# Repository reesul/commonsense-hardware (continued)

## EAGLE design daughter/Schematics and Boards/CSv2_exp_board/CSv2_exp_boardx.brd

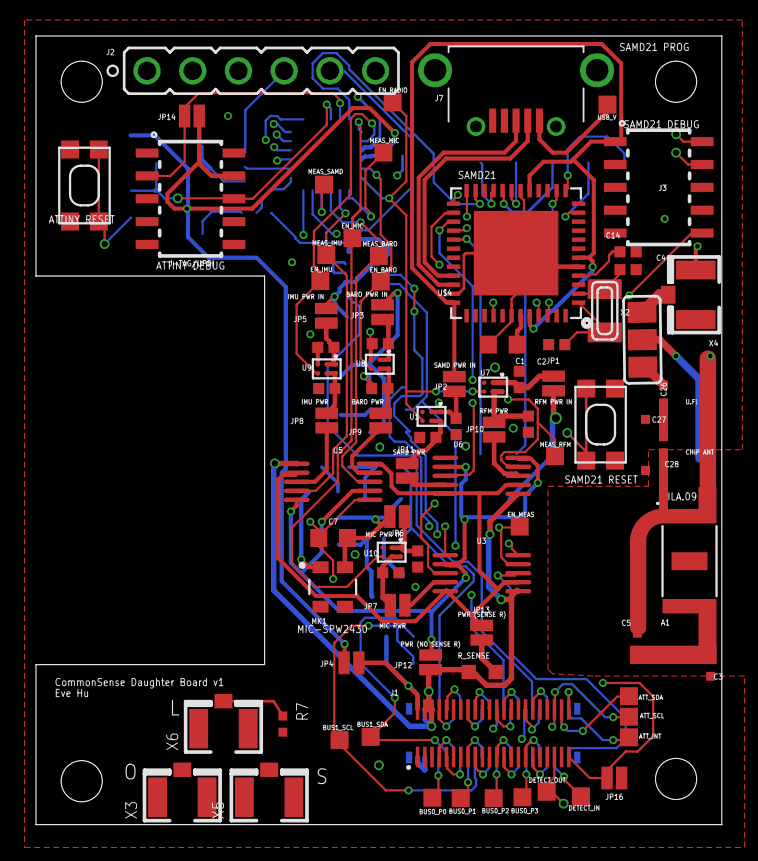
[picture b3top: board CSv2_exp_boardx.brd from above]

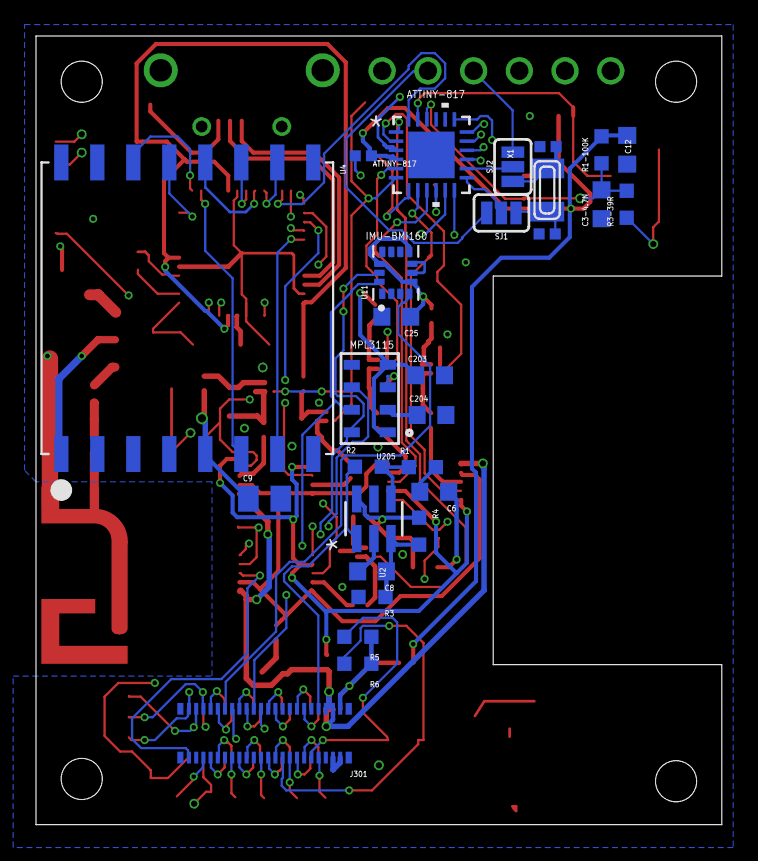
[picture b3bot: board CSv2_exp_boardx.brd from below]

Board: 4 copper layers, 38.1 x 43.8 mm, 112 parts (28 on the bottom side), 108 nets.

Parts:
A1: ILA09_CHIP_ANTENNA; ILA_09_CHIP_ANTENNA2
ATTINY-817: ATTINY817-MFRQFN24_RX4MC-L_ATTINY817-MFR; ATTINY817-MFRQFN24_RX4MC-L_QFN24_4X4MC
ATT_INT: TPTP10SQ; TP10SQ
ATT_SCL: TPTP10SQ; TP10SQ
ATT_SDA: TPTP10SQ; TP10SQ
BUS0_P0, BUS0_P1, BUS0_P2, BUS0_P3, BUS1_SCL, BUS1_SDA: TPTP10SQ; TP10SQ
C1: 1uF; C0603
C2, C4: 22pF; C0402
C3: 3.9p; C0402-S
C3-4.7N: 4.7n; C0603
C5: 2.2p; C0402-S
C6: 4.7u; C0603
C7: 0.1u; C0603
C8: 1u; C0603
C9: 10uF; C0805
C10, C17, C19, C21, C23: 1u; C0402
C11, C18, C20, C22, C24: 100n; C0402
C12: 4.7nF; C0603
C13: 100nF; C0402
C14: 1uF; C0402
C15, C16: 13pF; C0402
C25, C203, C204: 0.1uF; C0603
C26, C27, C28: C0402-S
DETECT_IN: TPTP10SQ; TP10SQ
DETECT_OUT: TPTP10SQ; TP10SQ
EN_BARO: TPTP10SQ; TP10SQ
EN_IMU: TPTP10SQ; TP10SQ
EN_MEAS: TPTP10SQ; TP10SQ
EN_MIC: TPTP10SQ; TP10SQ
EN_RADIO: TPTP10SQ; TP10SQ
J1: HIROSE-DF40_44-PIN_CONNECTORS-RECEPTACLE; HRS_DF40HC(3.0)-44DS-0.4V(51)
J2: J-SERIAL-PORT; HEADER-1X6
J3: CORTEX_DEBUG_SMD; SAMTECH_FTSH-105-01
J7: J-USB-HIROSE-MICRO-USB; USB-THRU-ZX62D-AB-5P8
J301: HIROSE-DF40_44-PIN_CONNECTORS-HEADER; HRS_DF40C-44DP-0.4V(51)
J-TAG/UPDI: ATTINY_AVR_DEBUG_SMD; ATTINY_AVR_DEBUG
JP1, JP2, JP3, JP4, JP5, JP6, JP7, JP8, JP9, JP10, JP11, JP12, JP13: JUMPER-SMT_2_NC_PASTELG_NO-SILK; SMT-JUMPER_2_NC_PASTE_NO-SILK
JP14, JP16: JUMPER-SMT_2_NO_PASTEFREE; SMT-JUMPER_2_NO_PASTEFREE_NO-SILK
L1: L0402
MEAS_BARO: TPTP10SQ; TP10SQ
MEAS_IMU: TPTP10SQ; TP10SQ
MEAS_MIC: TPTP10SQ; TP10SQ
MEAS_RFM: TPTP10SQ; TP10SQ
MEAS_SAMD: TPTP10SQ; TP10SQ
MK1: SPW2430HR5H-B; MIC_SPW2430HR5H-B
R1: 1.5k; R0603
R1-100K, R2: 100k; R0603
R3, R4: 10k; R0603
R3-39R: 39r; R0603
R5, R6: 4.7k; R0603
R7: R0402
R_SENSE: 1.33; R0603
SJ1, SJ2: JUMPER-SMT_3_1-NC_PASTE_SILK; SMT-JUMPER_3_1-NC_PASTE_SILK
SJ3: JUMPER_SJ_2
SW1, SW2: SPST_TACT-KMR2; KMR2
U1, U7, U8, U9, U10: LOADSWITCH-MIC94164; WLCSP6_2X3
U2: ADA4841-1YRJZ-R7; RJ_6
U3, U5, U6: Value; DGS0010A_L
U4: RFM69HCW; RFM-MOD
U11: BMI160; PQFN50P300X250X88-14N
U205: MPL3115A2; MPL3115A2_PSON125P300X500X120-8N
U$4: ATSAMD21G18_QFN; MICROBUILDER_TQFN48_7MM
USB_V: TPTP10SQ; TP10SQ
X1: 32.768kHz; ADAFRUIT2_XTAL3215
X2: 32.768; ADAFRUIT2_XTAL3215
X3, X4, X5, X6: uFL; U.FL

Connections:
+3V3_ATT: ATTINY-817.4, C12.2, C13.2, J-TAG/UPDI.4, JP4.2, JP14.1, R1-100K.2
+3V3_BARO: C203.1, JP3.2, U205.1, U205.4
+3V3_BARO_IN: C19.1, JP9.2, U8.A2, U8.B2
+3V3_BARO_OUT: C20.1, JP3.1, U8.A1, U8.B1
+3V3_BARO_PWR: JP9.1, U5.9
+3V3_DTR: J1.4, J1.6, J301.4, J301.6, JP12.1, R_SENSE.1, U3.1, U5.1, U6.1
+3V3_DTR0: J1.2, J301.2, JP4.1, R5.1, R6.1
+3V3_IMU: C25.1, JP5.2, U11.5, U11.8, U11.12
+3V3_IMU_IN: C21.1, JP8.2, U9.A2, U9.B2
+3V3_IMU_OUT: C22.1, JP5.1, U9.A1, U9.B1
+3V3_IMU_PWR: JP8.1, U5.3
+3V3_MEAS: JP13.2, U3.2, U3.10, U5.2, U5.10, U6.2, U6.10
+3V3_MIC: C7.1, JP6.2, MK1.4, R4.1, U2.6
+3V3_MIC_IN: C23.1, JP7.2, U10.A2, U10.B2
+3V3_MIC_OUT: C24.1, JP6.1, U10.A1, U10.B1
+3V3_MIC_PWR: JP7.1, U3.9
+3V3_NMEAS: JP12.2, U3.7, U5.5, U5.7, U6.5, U6.7
+3V3_RFM: C9.1, JP1.2, U4.5P
+3V3_RFM_IN: C17.1, JP10.2, U7.A2, U7.B2
+3V3_RFM_OUT: C18.1, JP1.1, U7.A1, U7.B1
+3V3_RFM_PWR: JP10.1, U6.3
+3V3_SAMD: J3.1, JP2.2, U$4.6, U$4.17, U$4.36, U$4.44
+3V3_SAMD_IN: C10.1, JP11.2, U1.A2, U1.B2
+3V3_SAMD_OUT: C11.1, JP2.1, U1.A1, U1.B1
+3V3_SAMD_PWR: JP11.1, U6.9
AREF: C14.1, U$4.4
ATT_INT: ATTINY-817.17, ATT_INT.TP, J1.44, J301.44
AT_RESET: ATTINY-817.22, C3-4.7N.2, J-TAG/UPDI.6, R1-100K.1, R3-39R.2
AT_UPDI: ATTINY-817.23, J-TAG/UPDI.3, JP14.2
BUS0_AIN0: J301.8, R2.1, U2.1
BUS0_GPIO0: ATTINY-817.24, J301.24, U$4.23
BUS0_GPIO1: J301.32, U$4.24
BUS0_SERCOM_P0: BUS0_P0.TP, J301.7, U$4.25
BUS0_SERCOM_P1: BUS0_P1.TP, J301.15, U$4.26
BUS0_SERCOM_P2: BUS0_P2.TP, J301.23, U$4.27
BUS0_SERCOM_P3: BUS0_P3.TP, J301.31, U$4.28
BUS1_GPIO0: J301.26, U205.6
BUS1_GPIO1: J301.34, U11.4
BUS1_SERCOM_P0: BUS1_SDA.TP, J301.9, R5.2, U11.14, U205.7
BUS1_SERCOM_P1: BUS1_SCL.TP, J301.17, R6.2, U11.13, U205.8
BUS2_AIN0: J1.8, J301.12
BUS2_AIN1: J1.16, J301.20
BUS2_GPIO0: J1.24, J301.28
BUS2_GPIO1: J1.32, J301.36
BUS2_SERCOM_P0: J1.7, J301.11
BUS2_SERCOM_P1: J1.15, J301.19
BUS2_SERCOM_P2: J1.23, J301.27
BUS2_SERCOM_P3: J1.31, J301.35
BUS3_AIN0: J1.10, J301.14
BUS3_AIN1: J1.18, J301.22
BUS3_GPIO0: J1.26, J301.30
BUS3_GPIO1: J1.34, J301.38
BUS3_SERCOM_P0: J1.9, J301.13
BUS3_SERCOM_P1: J1.17, J301.21
BUS3_SERCOM_P2: J1.25, J301.29
BUS3_SERCOM_P3: J1.33, J301.37
DTR_DETECT_IN: ATTINY-817.18, DETECT_IN.TP, J301.39
DTR_DETECT_OUT: ATTINY-817.19, DETECT_OUT.TP, J1.39
D_N: J7.D-, U$4.33
D_P: J7.D+, U$4.34
EN_BARO: ATTINY-817.5, EN_BARO.TP, U8.C2
EN_IMU: ATTINY-817.2, EN_IMU.TP, U9.C2
EN_MEAS: ATTINY-817.12, EN_MEAS.TP, U3.4
EN_MIC: ATTINY-817.1, EN_MIC.TP, U10.C2
EN_RADIO: ATTINY-817.6, EN_RADIO.TP, U1.C2, U7.C2
GND: A1.G1, ATTINY-817.3, C1.2, C2.2, C3.1, C3-4.7N.1, C4.2, C5.1, C7.2, C8.2, C9.2, C10.2, C11.2, C12.1, C13.1, C14.2, C15.1, C16.1, C17.2, C18.2, C19.2, C20.2, C21.2, C22.2, C23.2, C24.2, C25.2, C27.2, C28.1, C28.2, C203.2, C204.2, J1.1, J1.3, J1.5, J2.1, J3.3, J3.5, J7.GND, J7.S1, J7.S2, J7.S3, J7.S4, J301.1, J301.3, J301.5, J-TAG/UPDI.2, JP16.1, L1.2, MK1.2, MK1.3, R3.2, R7.2, SW1.1, SW1.3, SW2.1, SW2.3, U1.C1, U2.2, U3.6, U4.2P, U4.9P, U4.16P, U5.6, U6.6, U7.C1, U8.C1, U9.C1, U10.C1, U11.1, U11.6, U11.7, U205.3, U$4.5, U$4.18, U$4.35, U$4.42, U$4.THERMAL, X3.1, X3.2, X4.1, X4.2, X5.1, X5.2, X5.3, X6.1, X6.2
IN+: C8.1, R3.1, R4.2, U2.3
IN-: R1.1, R2.2, U2.4
LORA_CS: U4.13P, U$4.11
LORA_IRQ0: U4.6P, U$4.14
LORA_IRQ1: U4.7P, U$4.29
LORA_MISO: U4.10P, U$4.21
LORA_MOSI: U4.11P, U$4.19
LORA_RST: U4.14P, U$4.13
LORA_SCK: U4.12P, U$4.20
MASTER_I2C_SCL: ATTINY-817.16, ATT_SCL.TP, J1.40, J301.40
MASTER_I2C_SDA: ATTINY-817.15, ATT_SDA.TP, J1.42, J301.42
MEAS_BARO: ATTINY-817.9, MEAS_BARO.TP, U5.8
MEAS_IMU: ATTINY-817.8, MEAS_IMU.TP, U5.4
MEAS_MIC: ATTINY-817.7, MEAS_MIC.TP, U3.8
MEAS_RFM: ATTINY-817.11, MEAS_RFM.TP, U6.4
MEAS_SAMD: ATTINY-817.10, MEAS_SAMD.TP, U6.8
unnamed: C1.1, U$4.43
unnamed: SJ3.3, X4.3
unnamed: J2.5, SJ1.3
unnamed: A1.G2, C3.2, C5.2
unnamed: C2.1, U$4.1, X2.P$1
unnamed: C6.2, R1.2
unnamed: C4.1, U$4.2, X2.P$2
unnamed: JP13.1, R_SENSE.2
unnamed: C26.1, SJ3.1
unnamed: C204.1, U205.2
unnamed: R7.1, X6.3
unnamed: R3-39R.1, SW1.2, SW1.4
unnamed: C26.2, C27.1, L1.1
unnamed: J7.VBUS, USB_V.TP
unnamed: ATTINY-817.13, SJ1.2
unnamed: ATTINY-817.14, SJ2.2
unnamed: J2.4, SJ2.3
unnamed: C16.2, SJ1.1, X1.P$1
unnamed: C15.2, SJ2.1, X1.P$2
unnamed: SJ3.2, U4.1P
OUT: C6.1, MK1.1
SAMD_!RESET: J3.10, SW2.2, SW2.4, U$4.40
SWCLK: J3.4, U$4.45
SWDIO: J3.2, U$4.46
V_SENSE_IN: J1.43, JP16.2, U3.5
V_SENSE_OUT: J301.43, U3.3

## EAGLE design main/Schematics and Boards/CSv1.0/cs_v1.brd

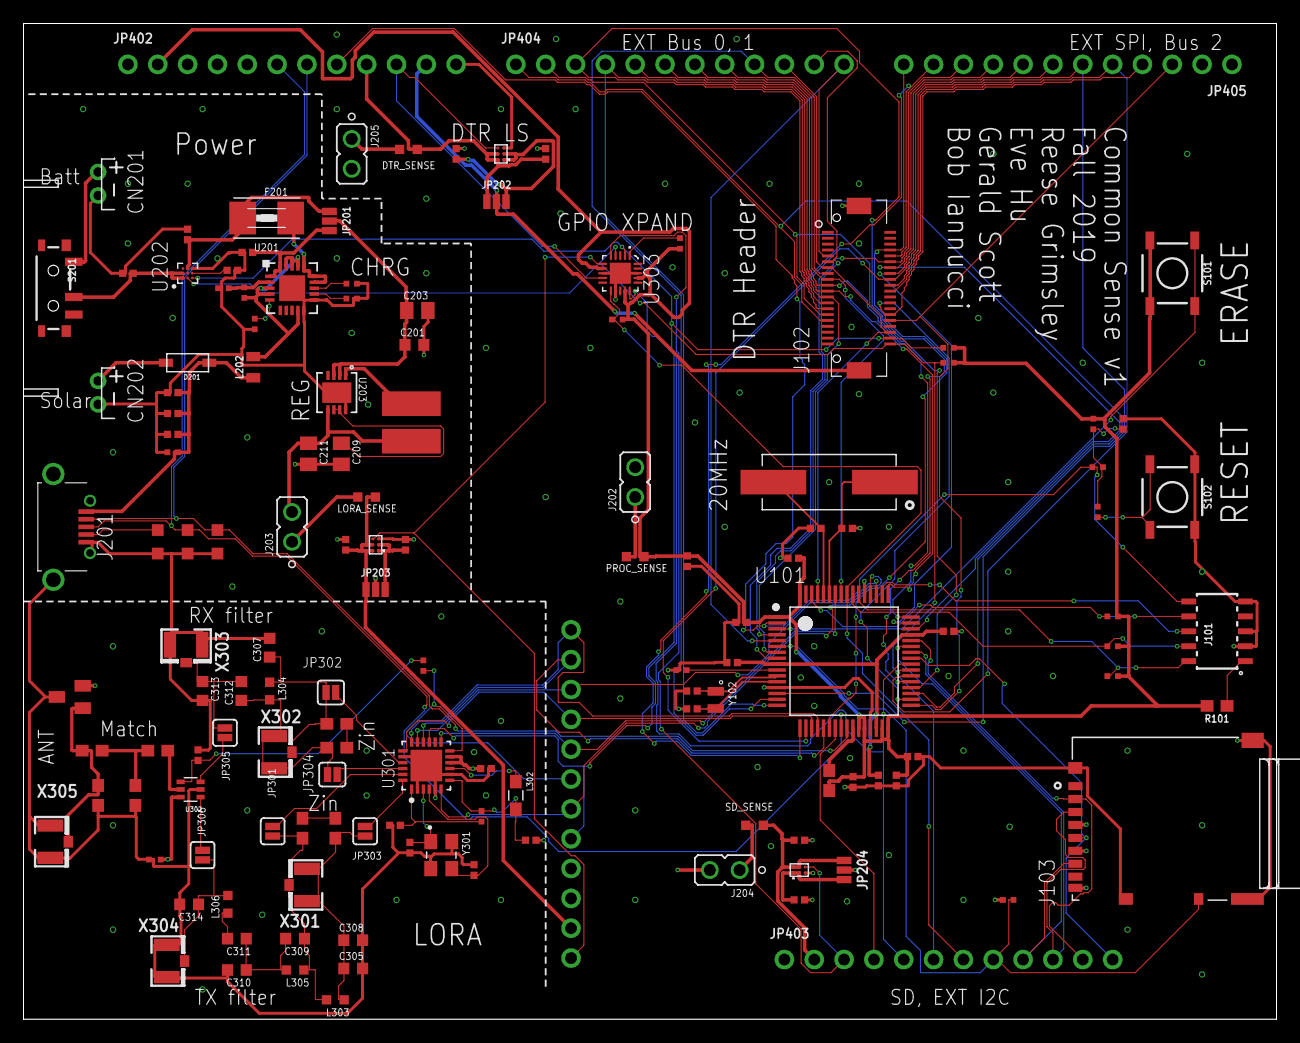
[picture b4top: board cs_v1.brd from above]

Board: 4 copper layers, 106.7 x 84.8 mm, 140 parts (1 on the bottom side), 119 nets.

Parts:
C101, C103: 5p; C0402
C102, C104: 16pF; C0402
C105, C208, C210: 4.7u; C0402
C106: 2.2u; C0402
C107, C108, C109, C110, C111, C112, C113, C114, C202, C215, C216, C217, C304: 100n; C0402
C201: 0.1uF; C0603
C203: 10uF; C0805
C204, C303: 10n; C0402
C205, C207: 10u; C0402
C206, C306: 470n; C0402
C209: 2.2uF; C0805
C211: 22uF; C0805
C212, C213, C214: 1u; C0402
C301, C302: 17p; C0402
C305: 47n; C0603
C307: 1.8p; C0603
C308: 47p; C0603
C309: 3.3p; C0603
C310: 8.2p; C0603
C311: 39p; C0603
C312: 2.4p; C0603
C313: 1.0p; C0603
C314: 3.0p; C0603
C315, C316: 1n; C0402
CN201: Battery; JST-PH-2-THM-RA
CN202: Solar; JST-PH-2-THM-RA
D201: MBR120VLSFT3GOSCT-ND; SOD-123
F201: MF-MSMF050-2; 1812
J101: CORTEX_DEBUG_SMD; SAMTECH_FTSH-105-01
J102: HIROSE-DF17(4.0)-40DS-0.5V(57); DF174040DS05V57_1
J103: DM3AT-SF-PEJM5; HRS_DM3AT-SF-PEJM5
J201: USBABSMTDIP; ZX62D-AB-5P8
J202, J203, J205: J-JUMPER; HEADER-1X2
J204: JMP_SD; HEADER-1X2
JP201: JMP_CHRG; SMT-JUMPER_3_NO_NO-SILK
JP202: JMP_DTR; SMT-JUMPER_3_NO_NO-SILK
JP203: JMP_LORA; SMT-JUMPER_3_NO_NO-SILK
JP204: JMP_SD; SMT-JUMPER_3_NO_NO-SILK
JP301, JP302, JP303, JP304, JP305, JP306: JUMPER-SMT_2_NO_SILK; SMT-JUMPER_2_NO_SILK
JP401, JP402, JP403, JP404, JP405: 1X12_ROUND
L201: 10uH; L-5X5SMD
L202: 3.3µH/±20%/450mA; 0805
L301: 47n; L0402
L302: 15u; INDC2012X87N
L303: 47n; L0603
L304: 15n; L0603
L305: 2.2n; L0603
L306: 9.1n; L0603
R101, R106, R301, R302, R303, R304, R307, R308, R309, R310: 0; 0603
R102, R103, R104, R105, R111, R202, R204: 100k; R0402
R107, R108: 4.7K; R0402
R109: 510k; R0402
R110, R112: 39; R0402
R201: 270k; R0402
R203: 2k; R0402
R205, R207, R208: CG0603MLC-05E; CT/CN0603
R206, R209, R305, R311: 10k; R0402
R210: 1.33; R0603
R211, R212: 1; R0603
R213: 0.5; R0603
R306: 1k; R0402
S101, S102: MOMENTARY-SWITCH-SPST-SMD-5.2-REDUNDANT; TACTILE_SWITCH_SMD_5.2MM
S201: SWITCH_SPST_SMD_A
U101: ATSAMG55J19A-AU; QFP50P1200X1200X160-64N
U201: U-MCP73871-2CCI/ML; QFN20_4X4MC
U202: COULOMB-MAX17262; BGA9N40P3X3_144X146X69N
U203: BUCK-LTC3624EDD-3.3PBF; DFN-8_DD
U204, U205, U206: LOADSWITCH-MIC94162; WLCSP6_2X3
U301: SEMTECH_SX1261IMLTRTSEMTECH_SX1261IMLTRT_0_0; SEMTECH_SX1261IMLTRT_0
U302: PE4259; SC-70
U303: EXPANDER-SX1502; UQFN20
U304: CM1213A-01SO; SOT23-3
X301, X302, X303, X304, X305: u.Fl; U.FL
Y101: ABLS2-20.000MHZ-D4Y-T; XTAL_ABLS2-20.000MHZ-D4Y-T
Y102: ABS06-32.768KHZ-T; XTAL_ABS06-32.768KHZ-T
Y301: ECS-32MHZ_CKM_XTAL; ECS-32MHZ_CKM-TR_XTAL

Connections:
3V3: C211.1, J202.2, J203.2, J204.2, J205.2, JP402.1, L201.2, U203.5
3V3_DTR: J102.42, JP202.2, JP402.11
3V3_DTR_LOAD: C214.1, JP202.1, JP402.9, R213.2, U204.A2, U204.B2
3V3_DTR_SW_OUT: C215.1, JP202.3, U204.A1, U204.B1
3V3_LORA: C304.1, C316.1, JP203.2, JP401.10, U301.10, U301.11, U302.6, U304.2
3V3_LORA_LOAD: C212.1, JP203.1, JP401.11, R210.2, U205.A2, U205.B2
3V3_LORA_SW_OUT: C216.1, JP203.3, U205.A1, U205.B1
3V3_PROC: C105.1, C109.1, C110.1, C111.1, C112.1, C113.1, JP402.2, R101.2, R102.2, R103.2, R105.2, R106.2, R107.2, R108.2, R111.2, R211.2, R305.2, R311.2, S101.3, S101.4, U101.1, U101.27, U101.28, U101.31, U101.32, U101.64, U303.7, U303.14, U303.17
3V3_SD: J103.4, JP204.2, JP403.1, R109.2
3V3_SD_LOAD: C213.1, JP204.1, JP403.2, R212.2, U206.A2, U206.B2
3V3_SD_SW_OUT: C217.1, JP204.3, U206.A1, U206.B1
3V7_BATTERY: C202.1, S201.2, U202.A1, U202.A2
3V7_BATTERY_LOAD: C210.1, F201.2, JP201.1, U202.B3
4V2: C208.1, JP201.3, U201.1, U201.20
ADDR_I2C_CLK: J102.40, JP403.6, R107.1, U101.39, U202.B1, U303.4
ADDR_I2C_DAT: J102.38, JP403.5, R108.1, U101.40, U202.C1, U303.2
BATT_IN: CN201.1, S201.3
BAT_CHG_PROG1: R203.2, U201.13
CHG_VPCC: R201.1, R202.2, U201.2
DAU_BRD_INT: JP403.4, U101.23
DEBUG_TCK: J101.4, R103.1, U101.55
DEBUG_TDI: J101.8, R105.1, U101.62
DEBUG_TDO: J101.6, U101.50
DEBUG_TEST: R104.2, U101.10
DEBUG_TMS: J101.2, R102.1, U101.54
DTR_JMP: J205.1, R213.1
EN_DTR: JP402.10, U204.C2, U303.9
EN_LORA: JP401.12, U205.C2, U303.6
EN_SD: JP403.3, U206.C2, U303.5
ERASE: S101.1, S101.2, U101.3
EXT_AD0: J102.32, JP405.3, U101.33
EXT_AD1: J102.30, JP405.4, U101.34
EXT_AD2: J102.31, JP404.1, U101.35
EXT_AD3: J102.29, JP404.2, U101.36
EXT_BUS0_GPIO_0/SPI_SCK: J102.27, JP404.3, U101.37
EXT_BUS0_GPIO_1: J102.25, JP404.4, U101.16
EXT_BUS0_INT: J102.23, JP404.5, U101.7
EXT_BUS0_RXD/SPI_MISO/TWCK/PDMIC_DAT: J102.21, JP404.6, U101.49
EXT_BUS0_TXD/SPI_MOSI/TWD/PDMIC_CLK: J102.19, JP404.7, U101.48
EXT_BUS1_GPIO_0/SPI_SCK: J102.17, JP404.8, U101.57
EXT_BUS1_GPIO_1: J102.15, JP404.9, U101.15
EXT_BUS1_INT: J102.13, J102.36, JP404.10, U101.61
EXT_BUS1_RXD/SPI_MISO/TWCK: J102.11, JP404.11, U101.4
EXT_BUS1_TXD/SPI_MOSI/TWD: J102.9, JP404.12, U101.5
EXT_BUS2_GPIO_0/SPI_SCK: J102.22, JP405.5, U101.38
EXT_BUS2_GPIO_1: J102.20, JP405.6, U101.14
EXT_BUS2_INT: J102.18, JP405.7, U101.18
EXT_BUS2_RXD/SPI_MISO/TWCK: J102.16, JP405.8, U101.47
EXT_BUS2_TXD/SPI_MOSI/TWD: J102.14, JP405.9, U101.46
EXT_SPI_MISO: J102.12, JP405.10, U101.8
EXT_SPI_MOSI: J102.10, JP405.11, U101.17
EXT_SPI_SCK: J102.8, JP405.12, U101.22
GND: C101.2, C102.2, C103.2, C104.2, C105.2, C106.2, C107.2, C108.2, C109.2, C110.2, C111.2, C112.2, C113.2, C114.2, C201.2, C202.2, C203.2, C204.2, C205.2, C206.2, C207.2, C208.2, C209.2, C210.2, C211.2, C212.2, C213.2, C214.2, C215.2, C216.2, C217.2, C301.2, C302.2, C303.1, C304.2, C305.2, C306.2, C307.2, C308.2, C310.2, C313.2, C314.2, C315.2, C316.2, CN201.2, CN202.2, J101.3, J101.5, J101.9, J102.41, J103.6, J103.P1, J103.P2, J103.P3, J103.P4, J103.SWB, J201.GND, J201.S1, J201.S2, J201.S3, J201.S4, JP402.12, R104.1, R202.1, R203.1, R204.1, R205.2, R206.1, R207.2, R208.2, R209.1, R308.1, R310.1, S102.3, S102.4, U101.13, U101.29, U101.53, U201.10, U201.11, U201.21, U202.C3, U203.8, U203.9, U204.C1, U205.C1, U206.C1, U301.2, U301.5, U301.8, U301.20, U301.25, U302.2, U303.8, U303.12, U303.18, U303.21, U304.3, X303.1, X303.2, X304.1, X304.2, X305.1, X305.2, Y301.2, Y301.4
LORA_DCC_SW: L302.1, U301.9
LORA_DIO1: JP401.5, U101.58, U301.13
LORA_DIO2: JP401.6, R306.1, U301.12
LORA_DIO3: JP401.7, U101.52, U301.6
LORA_JMP: J203.1, R210.1
LORA_RESET: JP401.8, U301.15, U303.15
LORA_RF: R309.2, R310.2, U304.1, X305.3
LORA_RF2_1: R307.2, R308.2, R309.1
LORA_RFI_N: C312.1, JP304.1, L304.2, R303.1, X302.1, X302.2
LORA_RFI_RX_SW: C312.2, C313.1, JP305.2, X303.3
LORA_RFO_4: C309.1, JP301.2, L303.2, L305.1, R301.1, X301.3
LORA_RFO_RX_SW: C314.1, JP306.2, L306.2, X304.3
LORA_RF_SW: R307.1, U302.5
LORA_RXTX_1: C315.1, R306.2, U302.4
LORA_VREG: C306.1, L301.1, L302.2, U301.7
LORA_XIN: C301.1, U301.3, Y301.1
LORA_XOUT: C302.1, U301.4, Y301.3
unnamed: JP301.1, U301.23
unnamed: L201.1, U203.1
unnamed: C309.2, C310.1, C311.1, L305.2
unnamed: J101.1, R101.1
unnamed: C311.2, L306.1
unnamed: C307.1, JP302.1, L304.1, R304.2, X302.3
unnamed: JP305.1, U302.3
unnamed: C209.1, U203.6, U203.7
unnamed: JP306.1, U302.1
unnamed: R204.2, U201.12
unnamed: JP304.2, U301.22
unnamed: C206.1, U202.C2
unnamed: JP303.2, U301.24
unnamed: JP302.2, U301.21
unnamed: R303.2, R304.1
unnamed: R301.2, R302.1
OTGID: J201.USBID, R205.1
PROC_JMP: J202.1, R211.1
PROC_RESET: J101.10, JP402.8, R112.2, U101.2
RESET_SW_1: C114.1, R110.2, R111.1, R112.1
RESET_SW_2: R110.1, S102.1, S102.2
SD_DETECT: J103.SWA, JP403.8, R109.1, U101.6
SD_JMP: J204.1, R212.1
SOLAR_V: CN202.1, D201.A
SPI_CS_LORA: JP401.4, U101.19, U301.19
SPI_CS_SD: J103.2, JP403.11, U101.44
SPI_MISO_LORA: JP401.3, U101.51, U301.17
SPI_MISO_SD: J103.7, JP403.9, U101.43
SPI_MOSI_LORA: JP401.2, U101.21, U301.16
SPI_MOSI_SD: J103.3, JP403.10, U101.42
SPI_SCK_LORA: JP401.1, U101.20, U301.18
SPI_SCK_SD: J103.5, JP403.12, U101.41
THERM: R206.2, U201.5
USB_D+: J201.D+, JP402.6, R207.1, U101.24
USB_D-: J201.D-, JP402.7, R208.1, U101.25
USB_VBUS: C204.1, C205.1, C207.1, D201.C, J201.VBUS, L202.1, R209.2
VBAT: F201.1, U201.14, U201.15, U201.16
VDDOUT: C106.1, C107.1, C108.1, U101.9, U101.30, U101.45
VDDUSB: R106.1, U101.26
VDD_LORA: C303.2, L301.2, U301.1
VREG_IN: C201.1, C203.1, JP201.2, U203.2, U203.3
VR_PA1: C305.1, C308.1, JP303.1, L303.1, R302.2, X301.1, X301.2
VSRC_RAW: L202.2, R201.2, U201.3, U201.4, U201.9, U201.17, U201.18, U201.19
XIN: C101.1, U101.59, Y101.1
XIN32: C102.1, U101.11, Y102.1
XOUT: C103.1, U101.60, Y101.2
XOUT32: C104.1, U101.12, Y102.2
XPAND_RST: R305.1, U303.1
XPAND_WKUP: JP403.7, R311.1, U101.56, U303.11
